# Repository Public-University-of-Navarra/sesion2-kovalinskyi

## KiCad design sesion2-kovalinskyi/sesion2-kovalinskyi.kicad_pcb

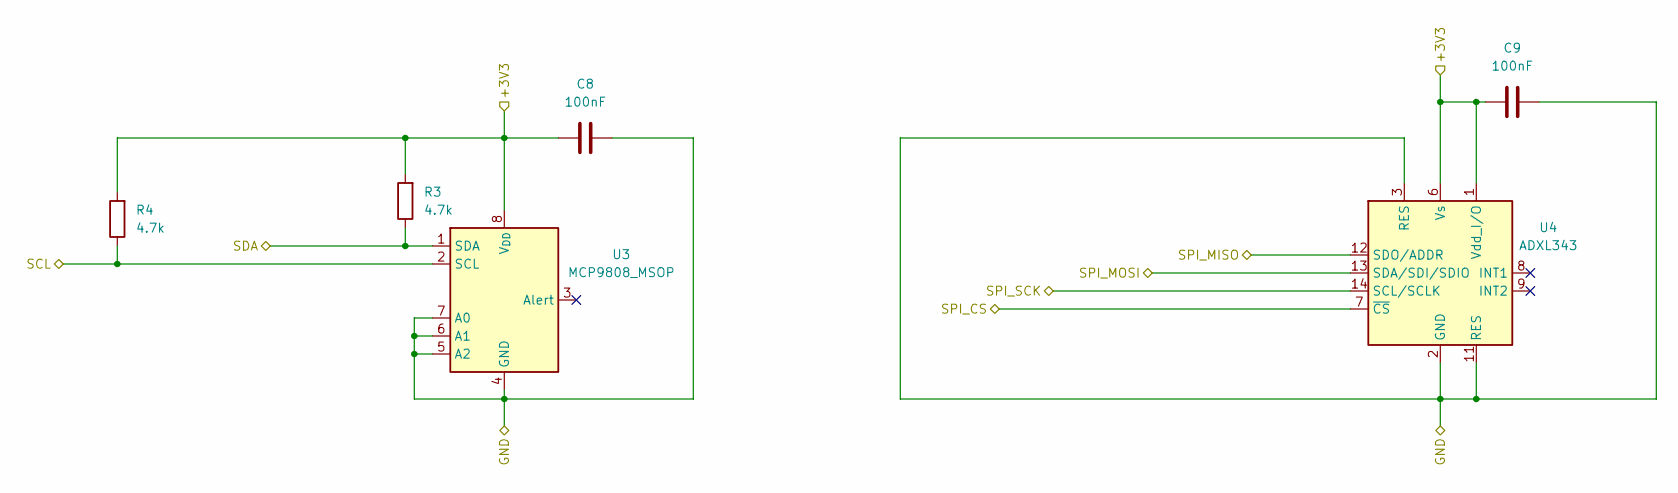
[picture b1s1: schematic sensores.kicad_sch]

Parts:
C8, C9: 100nF; C_0805_2012Metric; MPN CC0805KRX7R9BB104
R3, R4: 4.7k; R_0805_2012Metric; MPN RC0805FR-074K7L
U3: MCP9808_MSOP; MSOP-8_3x3mm_P0.65mm; MPN MCP9808-E/MS
U4: ADXL343; LGA-14_3x5mm_P0.8mm_LayoutBorder1x6y; MPN ADXL343BCCZ

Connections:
/UART-USB/+3V3: C8.2, C9.2, R3.2, R4.2, U3.8 (V_{DD}), U4.1 (Vdd_I/O), U4.6 (Vs); also elsewhere on the board
/UART-USB/GND: C8.1, C9.1, U3.4 (GND), U3.5 (A2), U3.6 (A1), U3.7 (A0), U4.2 (GND), U4.3 (RES), U4.4 (GND), U4.5 (GND), U4.11 (RES); also elsewhere on the board
/microcontrolador/SCL: R4.1, U3.2 (SCL); also elsewhere on the board
/microcontrolador/SDA: R3.1, U3.1 (SDA); also elsewhere on the board
/microcontrolador/SPI_CS: U4.7 (~CS); also elsewhere on the board
/microcontrolador/SPI_MISO: U4.12 (SDO/ADDR); also elsewhere on the board
/microcontrolador/SPI_MOSI: U4.13 (SDA/SDI/SDIO); also elsewhere on the board
/microcontrolador/SPI_SCK: U4.14 (SCL/SCLK); also elsewhere on the board

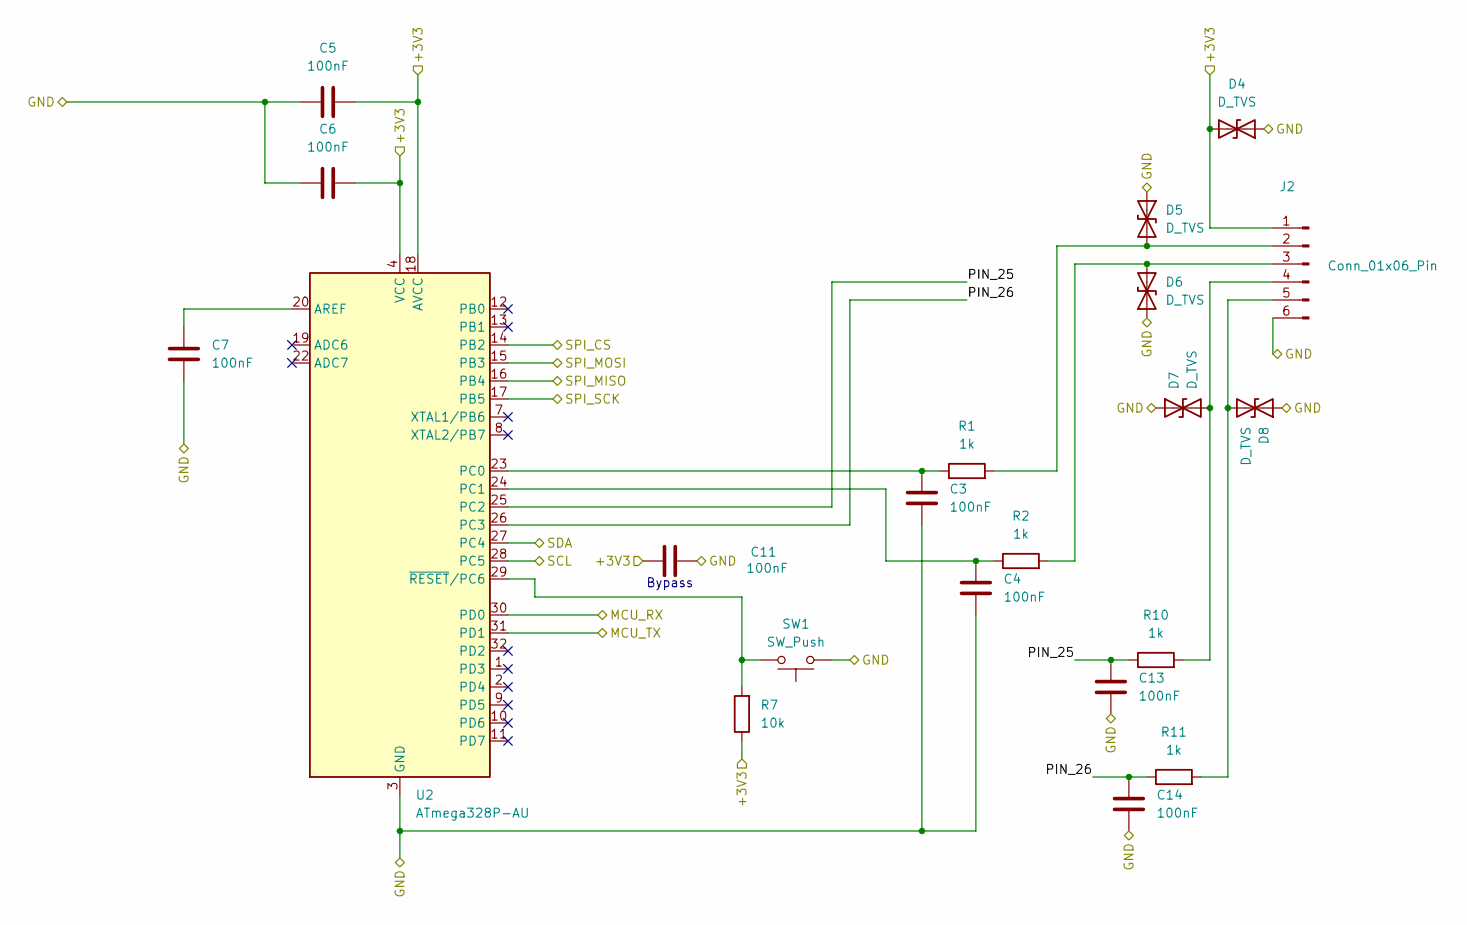
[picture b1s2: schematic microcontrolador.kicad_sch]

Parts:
C3, C4, C5, C6, C7, C11, C13, C14: 100nF; C_0805_2012Metric; MPN CC0805KRX7R9BB104
D4, D5, D6, D7, D8: D_TVS; D_SOD-123; MPN PESD3V3L1BA
J2: Conn_01x06_Pin; PinHeader_1x06_P2.54mm_Vertical; MPN PREC006SAAN-RC
R1, R2, R10, R11: 1k; R_0805_2012Metric; MPN RC0805FR-071KL
R7: 10k; R_0805_2012Metric; MPN RC0805FR-0710KL
SW1: SW_Push; SW_SPST_TL3342; MPN TL3342F160QG
U2: ATmega328P-AU; TQFP-32_7x7mm_P0.8mm; MPN ATMEGA328P-AU

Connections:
/UART-USB/+3V3: C5.1, C6.2, C11.1, D4.2 (A2), J2.1, R7.1, U2.4 (VCC), U2.6 (VCC), U2.18 (AVCC); also elsewhere on the board
/UART-USB/GND: C3.2, C4.2, C5.2, C6.1, C7.1, C11.2, C13.2, C14.2, D4.1 (A1), D5.1 (A1), D6.1 (A1), D7.1 (A1), D8.1 (A1), J2.6, SW1.1, U2.3 (GND), U2.5 (GND), U2.21 (GND); also elsewhere on the board
/UART-USB/MCU_RX: U2.30 (PD0); also elsewhere on the board
/UART-USB/MCU_TX: U2.31 (PD1); also elsewhere on the board
/microcontrolador/PIN_25: C13.1, R10.1, U2.25 (PC2)
/microcontrolador/PIN_26: C14.1, R11.1, U2.26 (PC3)
/microcontrolador/SCL: U2.28 (PC5); also elsewhere on the board
/microcontrolador/SDA: U2.27 (PC4); also elsewhere on the board
/microcontrolador/SPI_CS: U2.14 (PB2); also elsewhere on the board
/microcontrolador/SPI_MISO: U2.16 (PB4); also elsewhere on the board
/microcontrolador/SPI_MOSI: U2.15 (PB3); also elsewhere on the board
/microcontrolador/SPI_SCK: U2.17 (PB5); also elsewhere on the board
unnamed: D5.2 (A2), J2.2, R1.2
unnamed: D6.2 (A2), J2.3, R2.2
unnamed: D7.2 (A2), J2.4, R10.2
unnamed: D8.2 (A2), J2.5, R11.2
unnamed: C7.2, U2.20 (AREF)
unnamed: C3.1, R1.1, U2.23 (PC0)
unnamed: C4.1, R2.1, U2.24 (PC1)
unnamed: R7.2, SW1.2, U2.29 (~RESET/PC6)

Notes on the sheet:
Bypass

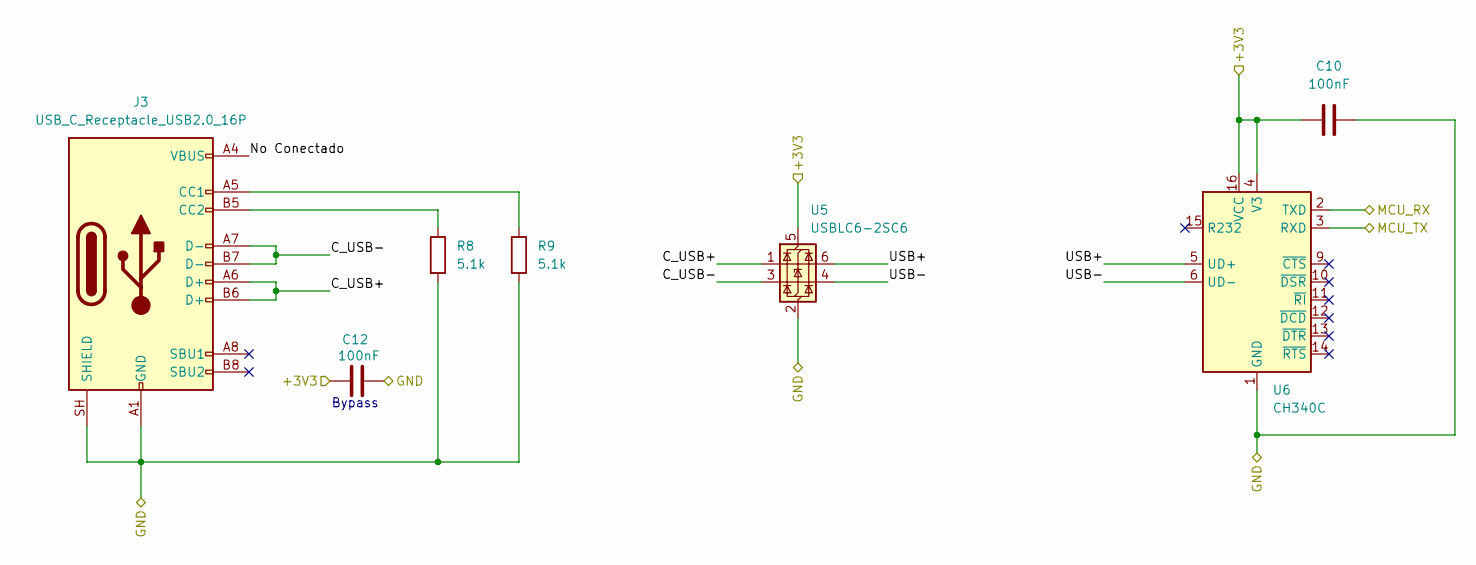
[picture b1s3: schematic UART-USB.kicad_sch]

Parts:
C10, C12: 100nF; C_0805_2012Metric; MPN CC0805KRX7R9BB104
J3: USB_C_Receptacle_USB2.0_16P; USB_C_Receptacle_HRO_TYPE-C-31-M-12; MPN TYPE-C-31-M-12
R8, R9: 5.1k; R_0805_2012Metric; MPN RC0805FR-075K1L
U5: USBLC6-2SC6; SOT-23-6; MPN USBLC6-2SC6
U6: CH340C; SOIC-16_3.9x9.9mm_P1.27mm; MPN CH340C

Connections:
/UART-USB/+3V3: C10.2, C12.1, U5.5 (VBUS), U6.4 (V3), U6.16 (VCC); also elsewhere on the board
/UART-USB/C_USB+: J3.A6 (D+), J3.B6 (D+), U5.1 (I/O1)
/UART-USB/C_USB-: J3.A7 (D-), J3.B7 (D-), U5.3 (I/O2)
/UART-USB/GND: C10.1, C12.2, J3.A1 (GND), J3.A12 (GND), J3.B1 (GND), J3.B12 (GND), J3.SH (SHIELD), R8.2, R9.2, U5.2 (GND), U6.1 (GND); also elsewhere on the board
/UART-USB/MCU_RX: U6.2 (TXD); also elsewhere on the board
/UART-USB/MCU_TX: U6.3 (RXD); also elsewhere on the board
/UART-USB/No Conectado: J3.A4 (VBUS), J3.A9 (VBUS), J3.B4 (VBUS), J3.B9 (VBUS)
/UART-USB/USB+: U5.6 (I/O1), U6.5 (UD+)
/UART-USB/USB-: U5.4 (I/O2), U6.6 (UD-)
unnamed: J3.A5 (CC1), R9.1
unnamed: J3.B5 (CC2), R8.1

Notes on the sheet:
Bypass

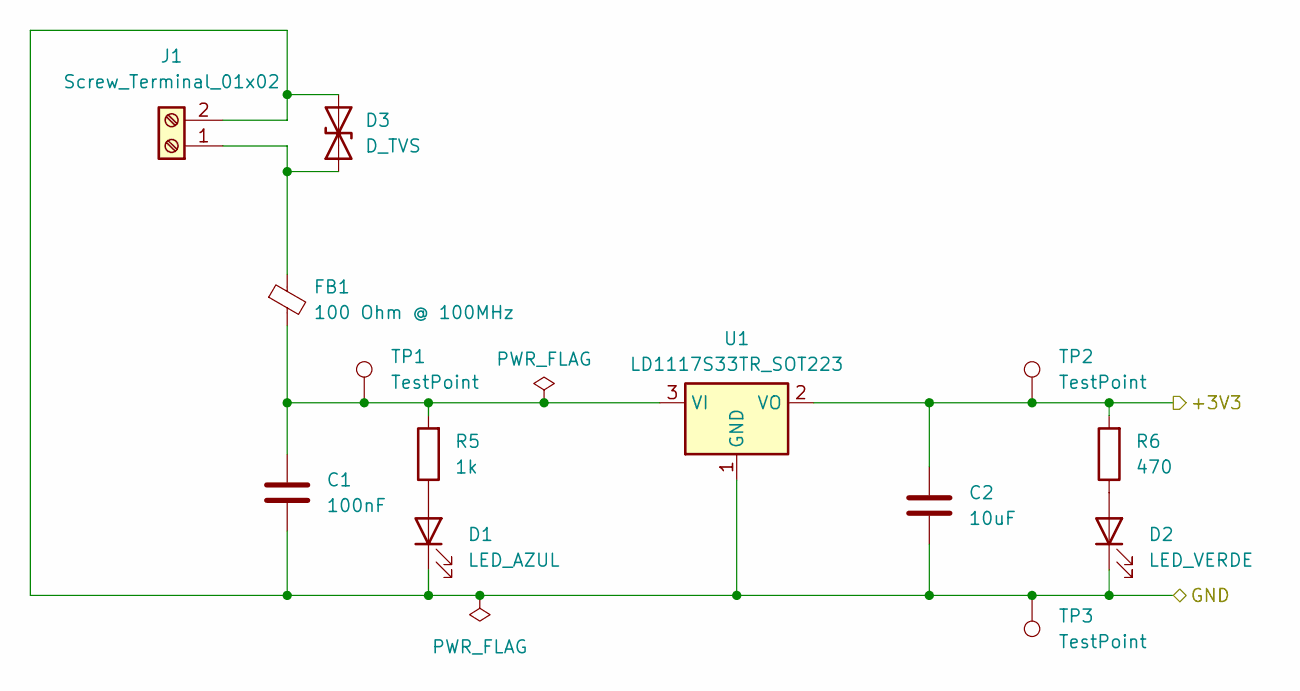
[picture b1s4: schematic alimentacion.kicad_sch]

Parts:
C1: 100nF; C_0805_2012Metric; MPN CC0805KRX7R9BB104
C2: 10uF; C_0805_2012Metric; MPN CC0805MKX5R7BB106
D1: LED_AZUL; LED_0805_2012Metric; MPN 150080BS75000
D2: LED_VERDE; LED_0805_2012Metric; MPN 150080VS75000
D3: D_TVS; D_SOD-123; MPN PESD3V3L1BA
FB1: 100 Ohm @ 100MHz; R_0805_2012Metric; MPN BLM21PG221SN1D
J1: Screw_Terminal_01x02; TerminalBlock_Phoenix_MPT-0,5-2-2.54_1x02_P2.54mm_Horizontal; MPN 1725656
R5: 1k; R_0805_2012Metric; MPN RC0805FR-071KL
R6: 470; R_0805_2012Metric; MPN RC0805FR-07470RL
TP1, TP2, TP3: TestPoint; TestPoint_Pad_D1.5mm
U1: LD1117S33TR_SOT223; SOT-223-3_TabPin2; MPN LD1117S33TR

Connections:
/UART-USB/+3V3: C2.2, R6.2, TP2.1 (1_1), U1.2 (VO); also elsewhere on the board
/UART-USB/GND: C1.1, C2.1, D1.1 (K), D2.1 (K), D3.2 (A2), J1.2, TP3.1 (1_1), U1.1 (GND); also elsewhere on the board
unnamed: D1.2 (A), R5.1
unnamed: D2.2 (A), R6.1
unnamed: D3.1 (A1), FB1.1, J1.1
unnamed: C1.2, FB1.2, R5.2, TP1.1 (1_1), U1.3 (VI)

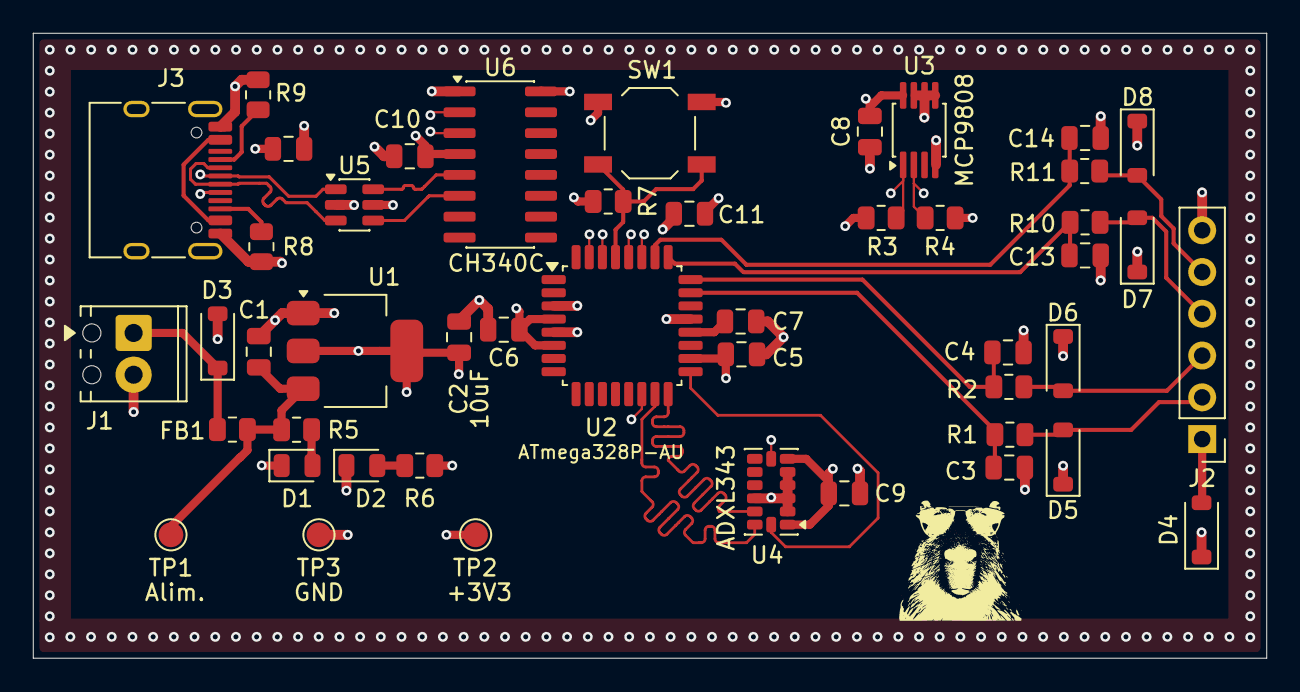
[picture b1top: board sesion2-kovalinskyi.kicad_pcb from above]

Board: 4 copper layers, 75.0 x 38.0 mm, 47 parts (0 on the bottom side), 31 nets.
